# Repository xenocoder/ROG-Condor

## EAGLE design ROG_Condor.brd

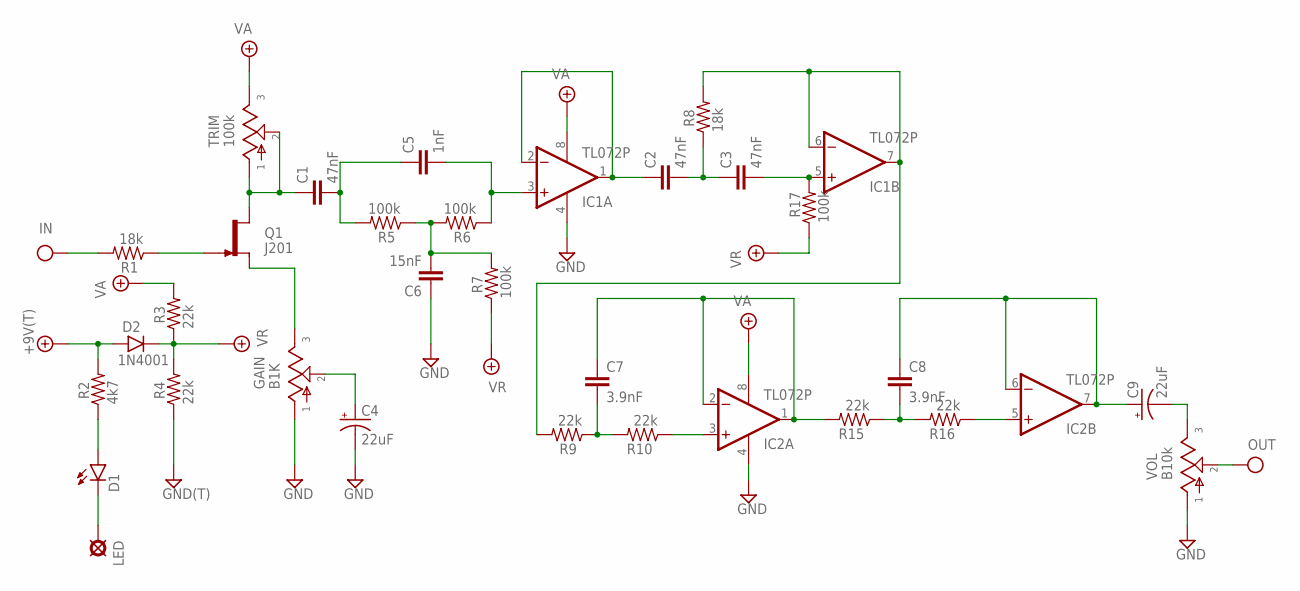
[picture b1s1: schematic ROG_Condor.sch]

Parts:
+9V: +9V(T); SQUARE
C1, C2, C3: 47nF; 075X040
C4, C9: 22uF; 050_020_1
C5: 1nF; 075X040
C6: 15nF; 075X040
C7, C8: 3.9nF; 075X040
D1: LED3MM
D2: 1N4001; DO41-3
GAIN: B1K; 16MM
GND: GND(T); SQUARE
IC1, IC2: TL072P; DIL08
IN: IN(T); SQUARE
LED: LED; SQUARE
OUT: OUT(T); SQUARE
Q1: J201; TO92-
R1, R8: 18k; R0207/3
R2: 4k7; R0207/3
R3, R4, R9, R10, R15, R16: 22k; R0207/3
R5, R6, R7, R17: 100k; R0207/3
TRIM: 100k; B25P
VOL: B10k; 16MM

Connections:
+9V: +9V.1, D2.A, R2.2
GND: C4.-, C6.1, GAIN.1, GND.1, IC1.4 (V-), IC2.4 (V-), R4.1, VOL.1
IN: IN.1, R1.2
unnamed: C7.2, R9.1, R10.2
unnamed: IC2.3 (+IN), R10.1
unnamed: Q1.1 (G), R1.1
unnamed: C1.1, Q1.3 (D), TRIM.1, TRIM.2
unnamed: D1.A, R2.1
unnamed: D1.K (C), LED.1
unnamed: C4.+, GAIN.2
unnamed: GAIN.3, Q1.2 (S)
unnamed: C1.2, C5.1, R5.2
unnamed: C5.2, IC1.3 (+IN), R6.1
unnamed: C2.1, IC1.1 (OUT), IC1.2 (-IN)
unnamed: C6.2, R5.1, R6.2, R7.2
unnamed: C2.2, C3.1, R8.1
unnamed: C3.2, IC1.5 (+IN), R17.2
unnamed: IC1.6 (-IN), IC1.7 (OUT), R8.2, R9.2
unnamed: C7.1, IC2.1 (OUT), IC2.2 (-IN), R15.2
unnamed: C8.2, R15.1, R16.2
unnamed: IC2.5 (+IN), R16.1
unnamed: C8.1, C9.+, IC2.6 (-IN), IC2.7 (OUT)
unnamed: C9.-, VOL.3
OUT: OUT.1, VOL.2
VA: IC1.8 (V+), IC2.8 (V+), R3.2, TRIM.3
VR: D2.C, R3.1, R4.2, R7.1, R17.1

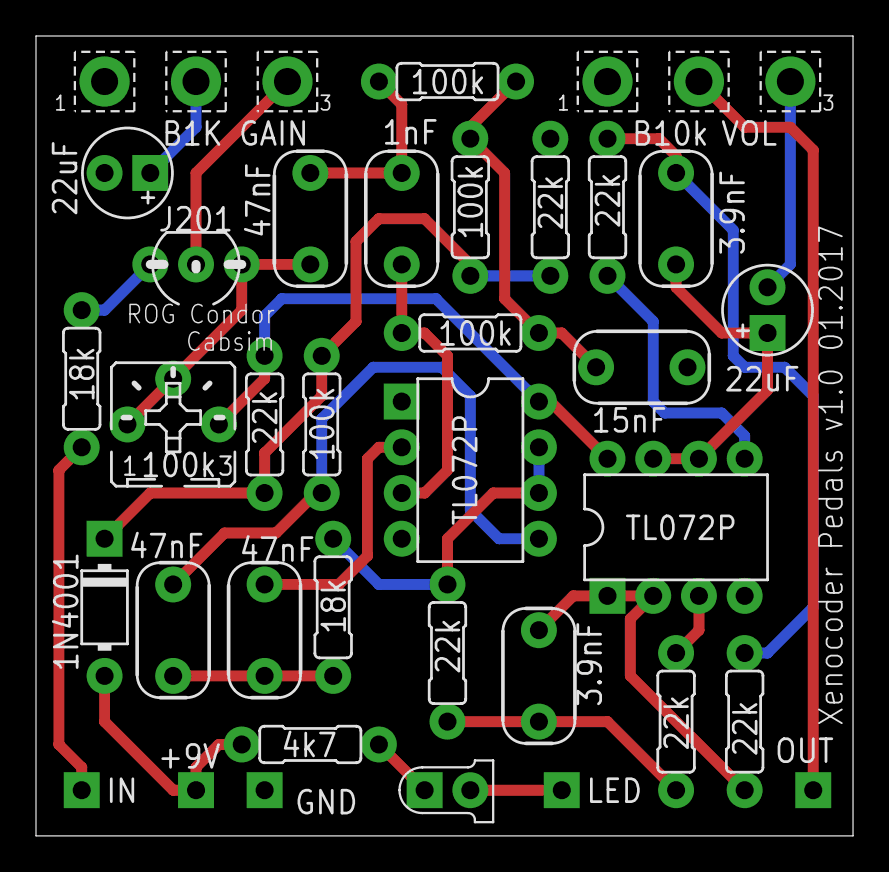
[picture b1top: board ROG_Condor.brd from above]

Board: 2 copper layers, 45.4 x 44.4 mm, 35 parts (0 on the bottom side), 26 nets.

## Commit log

2017-01-04 First commit on Version 1,0 files
2017-01-04 Updated layout and almost done version 1.0
2017-01-05 Version 1.0 with layout sent to OSHPark
